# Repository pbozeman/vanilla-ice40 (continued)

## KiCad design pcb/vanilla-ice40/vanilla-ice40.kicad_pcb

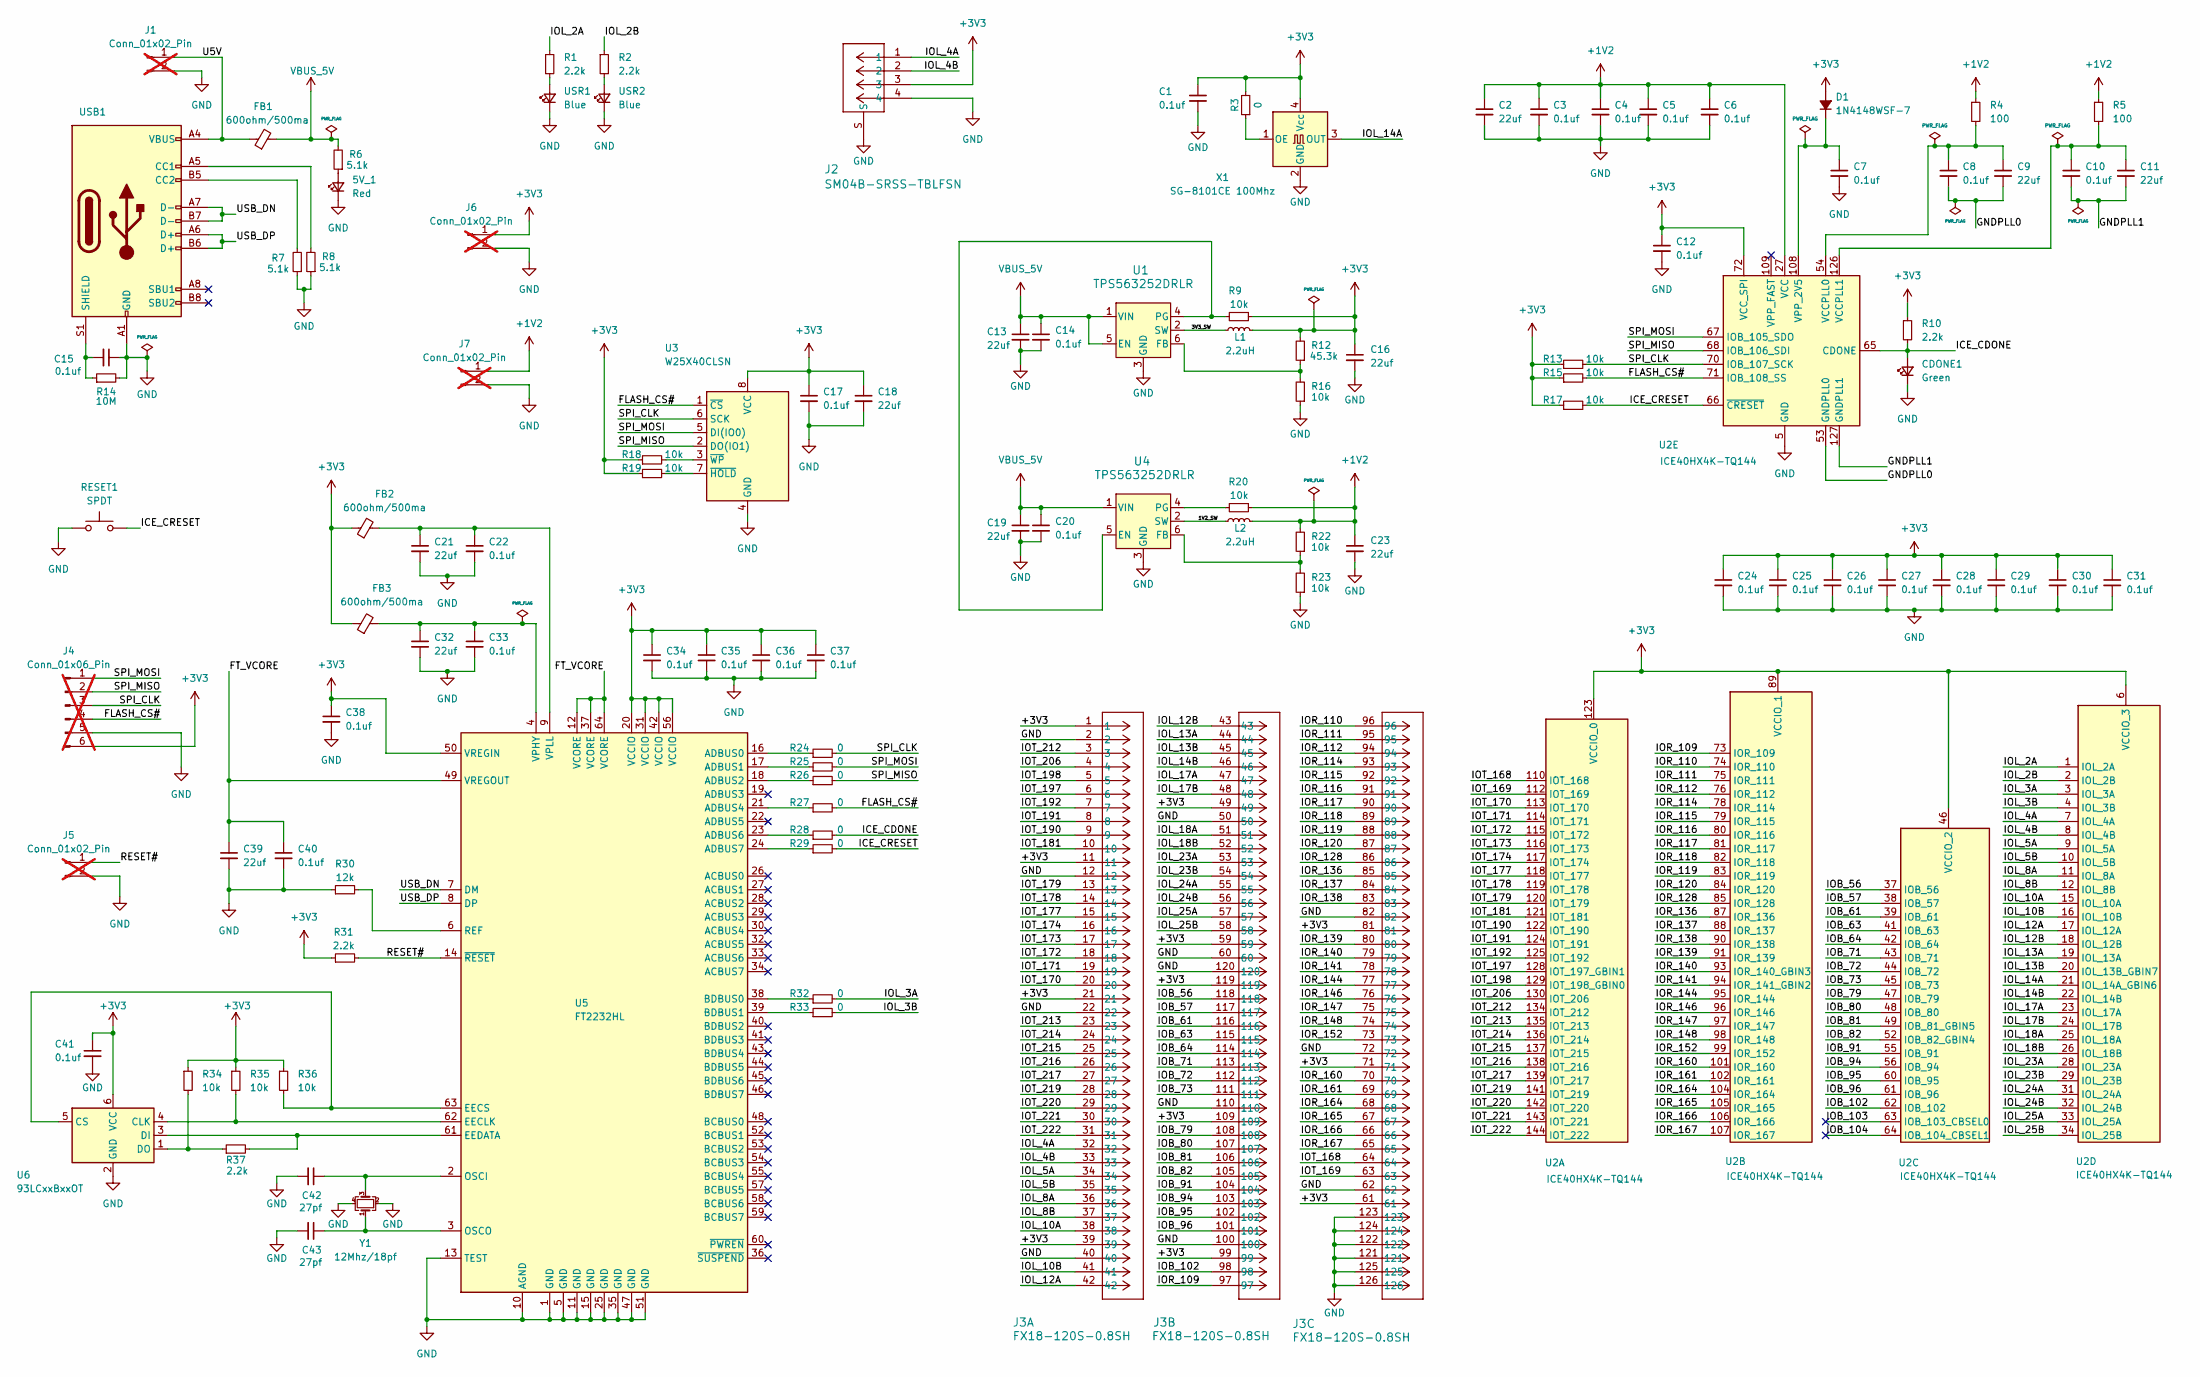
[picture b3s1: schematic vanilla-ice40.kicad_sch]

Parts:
5V_1: Red; D_0603_1608Metric; LCSC Part # C2286
C1, C3, C4, C5, C6, C7, C8, C10, C12, C14, C15, C17, C20, C22, C24, C25, C26, C27, C28, C29, C30, C31, C33, C34, C35, C36, C37, C38, C40, C41: 0.1uf; C_0402_1005Metric; LCSC Part # C1525
C2, C9, C11, C13, C16, C18, C19, C21, C23, C32, C39: 22uf; C_0603_1608Metric; LCSC Part # C59461
C42, C43: 27pf; C_0402_1005Metric; LCSC Part # C1555
CDONE1: Green; D_0603_1608Metric; LCSC Part # C434423
D1: 1N4148WSF-7; D_SOD-323F; LCSC Part # C119617
FB1, FB2, FB3: 600ohm/500ma; L_0603_1608Metric; LCSC Part # C1002
J1, J5, J6, J7: Conn_01x02_Pin; PinHeader_1x02_P2.54mm_Vertical; not fitted
J2: SM04B-SRSS-TBLFSN; CONN_SM04B_JST; LCSC Part # C160404
J3: FX18-120S-0.8SH; CUSTOM_FX_120S-0.8SH20; LCSC Part # C598059
J4: Conn_01x06_Pin; PinHeader_1x06_P2.54mm_Vertical; not fitted
L1, L2: 2.2uH; L_1008_2520Metric; LCSC Part # C391305
R1, R2, R10, R31, R37: 2.2k; R_0603_1608Metric; LCSC Part # C4190
R3, R24, R25, R26, R27, R28, R29, R32, R33: 0; R_0603_1608Metric; LCSC Part # C21189
R4, R5: 100; R_0603_1608Metric; LCSC Part # C22775
R6, R7, R8: 5.1k; R_0603_1608Metric; LCSC Part # C23186
R9, R13, R15, R16, R17, R18, R19, R20, R22, R23, R34, R35, R36: 10k; R_0603_1608Metric; LCSC Part # C25804
R12: 45.3k; R_0603_1608Metric; LCSC Part # C23058
R14: 10M; R_0603_1608Metric; LCSC Part # C7250
R30: 12k; R_0603_1608Metric; LCSC Part # C22790
RESET1: SPDT; SW_SPST_PTS810; LCSC Part # C221897
U1, U4: TPS563252DRLR; SOT6_DRL_TEX; LCSC Part # C19188399
U2: ICE40HX4K-TQ144; TQFP-144_20x20mm_P0.5mm; LCSC Part # C1521989
U3: W25X40CLSN; SOIC-8_3.9x4.9mm_P1.27mm; LCSC Part # C19617
U5: FT2232HL; LQFP-64_10x10mm_P0.5mm; LCSC Part # C27882
U6: 93LCxxBxxOT; SOT-23-6; LCSC Part # C190271
USB1: USB_C_Receptacle_USB2.0_16P; USB_C_Receptacle_GCT_USB4105-xx-A_16P_TopMnt_Horizontal; LCSC Part # C2686968
USR1, USR2: Blue; D_0603_1608Metric; LCSC Part # C965807
X1: SG-8101CE 100Mhz; Oscillator_SMD_SeikoEpson_SG8002CE-4Pin_3.2x2.5mm; LCSC Part # C390559
Y1: 12Mhz/18pf; Crystal_SMD_3225-4Pin_3.2x2.5mm; LCSC Part # C390764

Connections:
+1V2: C2.1, C3.1, C4.1, C5.1, C6.1, C23.1, J7.1, L2.2, R4.1, R5.1, R20.1, R22.2, U2.27 (VCC), U2.40 (VCC), U2.92 (VCC), U2.111 (VCC)
+3V3: C1.1, C12.1, C16.1, C17.1, C18.1, C24.1, C25.1, C26.1, C27.1, C28.1, C29.1, C30.1, C31.1, C34.1, C35.1, C36.1, C37.1, C38.1, C41.1, D1.2 (A), FB2.1, FB3.1, J2.3, J3.1, J3.11, J3.21, J3.39, J3.49, J3.59, J3.61, J3.71, J3.81, J3.99, J3.109, J3.119, J4.6, J6.1, L1.2, R3.2, R9.1, R10.1, R12.2, R13.1, R15.1, R17.1, R18.1, R19.1, R31.1, R34.1, R35.1, R36.1, U2.6 (VCCIO_3), U2.30 (VCCIO_3), U2.46 (VCCIO_2), U2.57 (VCCIO_2), U2.72 (VCC_SPI), U2.89 (VCCIO_1), U2.100 (VCCIO_1), U2.123 (VCCIO_0), U2.131 (VCCIO_0), U3.8 (VCC), U5.20 (VCCIO), U5.31 (VCCIO), U5.42 (VCCIO), U5.50 (VREGIN), U5.56 (VCCIO), U6.6 (VCC), X1.4 (Vcc)
/1V2_SW: L2.1, U4.2 (SW)
/3V3_SW: L1.1, U1.2 (SW)
/FLASH_CS#: J4.4, R15.2, R27.2, U2.71 (IOB_108_SS), U3.1 (~CS)
/FT_VCORE: C39.1, C40.1, U5.12 (VCORE), U5.37 (VCORE), U5.49 (VREGOUT), U5.64 (VCORE)
/GNDPLL0: C8.2, C9.2, U2.53 (GNDPLL0)
/GNDPLL1: C10.2, C11.2, U2.127 (GNDPLL1)
/ICE_CDONE: CDONE1.2 (A), R10.2, R28.2, U2.65 (CDONE)
/ICE_CRESET: R17.2, R29.2, RESET1.2, U2.66 (~CRESET)
/IOB_56: J3.118, U2.37 (IOB_56)
/IOB_57: J3.117, U2.38 (IOB_57)
/IOB_61: J3.116, U2.39 (IOB_61)
/IOB_63: J3.115, U2.41 (IOB_63)
/IOB_64: J3.114, U2.42 (IOB_64)
/IOB_71: J3.113, U2.43 (IOB_71)
/IOB_72: J3.112, U2.44 (IOB_72)
/IOB_73: J3.111, U2.45 (IOB_73)
/IOB_79: J3.108, U2.47 (IOB_79)
/IOB_80: J3.107, U2.48 (IOB_80)
/IOB_81: J3.106, U2.49 (IOB_81_GBIN5)
/IOB_82: J3.105, U2.52 (IOB_82_GBIN4)
/IOB_91: J3.104, U2.55 (IOB_91)
/IOB_94: J3.103, U2.56 (IOB_94)
/IOB_95: J3.102, U2.60 (IOB_95)
/IOB_96: J3.101, U2.61 (IOB_96)
/IOB_102: J3.98, U2.62 (IOB_102)
/IOB_103: U2.63 (IOB_103_CBSEL0)
/IOB_104: U2.64 (IOB_104_CBSEL1)
/IOL_2A: R1.1, U2.1 (IOL_2A)
/IOL_2B: R2.1, U2.2 (IOL_2B)
/IOL_3A: R32.2, U2.3 (IOL_3A)
/IOL_3B: R33.2, U2.4 (IOL_3B)
/IOL_4A: J2.1, J3.32, U2.7 (IOL_4A)
/IOL_4B: J2.2, J3.33, U2.8 (IOL_4B)
/IOL_5A: J3.34, U2.9 (IOL_5A)
/IOL_5B: J3.35, U2.10 (IOL_5B)
/IOL_8A: J3.36, U2.11 (IOL_8A)
/IOL_8B: J3.37, U2.12 (IOL_8B)
/IOL_10A: J3.38, U2.15 (IOL_10A)
/IOL_10B: J3.41, U2.16 (IOL_10B)
/IOL_12A: J3.42, U2.17 (IOL_12A)
/IOL_12B: J3.43, U2.18 (IOL_12B)
/IOL_13A: J3.44, U2.19 (IOL_13A)
/IOL_13B: J3.45, U2.20 (IOL_13B_GBIN7)
/IOL_14A: U2.21 (IOL_14A_GBIN6), X1.3 (OUT)
/IOL_14B: J3.46, U2.22 (IOL_14B)
/IOL_17A: J3.47, U2.23 (IOL_17A)
/IOL_17B: J3.48, U2.24 (IOL_17B)
/IOL_18A: J3.51, U2.25 (IOL_18A)
/IOL_18B: J3.52, U2.26 (IOL_18B)
/IOL_23A: J3.53, U2.28 (IOL_23A)
/IOL_23B: J3.54, U2.29 (IOL_23B)
/IOL_24A: J3.55, U2.31 (IOL_24A)
/IOL_24B: J3.56, U2.32 (IOL_24B)
/IOL_25A: J3.57, U2.33 (IOL_25A)
/IOL_25B: J3.58, U2.34 (IOL_25B)
/IOR_109: J3.97, U2.73 (IOR_109)
/IOR_110: J3.96, U2.74 (IOR_110)
/IOR_111: J3.95, U2.75 (IOR_111)
/IOR_112: J3.94, U2.76 (IOR_112)
/IOR_114: J3.93, U2.78 (IOR_114)
/IOR_115: J3.92, U2.79 (IOR_115)
/IOR_116: J3.91, U2.80 (IOR_116)
/IOR_117: J3.90, U2.81 (IOR_117)
/IOR_118: J3.89, U2.82 (IOR_118)
/IOR_119: J3.88, U2.83 (IOR_119)
/IOR_120: J3.87, U2.84 (IOR_120)
/IOR_128: J3.86, U2.85 (IOR_128)
/IOR_136: J3.85, U2.87 (IOR_136)
/IOR_137: J3.84, U2.88 (IOR_137)
/IOR_138: J3.83, U2.90 (IOR_138)
/IOR_139: J3.80, U2.91 (IOR_139)
/IOR_140: J3.79, U2.93 (IOR_140_GBIN3)
/IOR_141: J3.78, U2.94 (IOR_141_GBIN2)
/IOR_144: J3.77, U2.95 (IOR_144)
/IOR_146: J3.76, U2.96 (IOR_146)
/IOR_147: J3.75, U2.97 (IOR_147)
/IOR_148: J3.74, U2.98 (IOR_148)
/IOR_152: J3.73, U2.99 (IOR_152)
/IOR_160: J3.70, U2.101 (IOR_160)
/IOR_161: J3.69, U2.102 (IOR_161)
/IOR_164: J3.68, U2.104 (IOR_164)
/IOR_165: J3.67, U2.105 (IOR_165)
/IOR_166: J3.66, U2.106 (IOR_166)
/IOR_167: J3.65, U2.107 (IOR_167)
/IOT_168: J3.64, U2.110 (IOT_168)
/IOT_169: J3.63, U2.112 (IOT_169)
/IOT_170: J3.20, U2.113 (IOT_170)
/IOT_171: J3.19, U2.114 (IOT_171)
/IOT_172: J3.18, U2.115 (IOT_172)
/IOT_173: J3.17, U2.116 (IOT_173)
/IOT_174: J3.16, U2.117 (IOT_174)
/IOT_177: J3.15, U2.118 (IOT_177)
/IOT_178: J3.14, U2.119 (IOT_178)
/IOT_179: J3.13, U2.120 (IOT_179)
/IOT_181: J3.10, U2.121 (IOT_181)
/IOT_190: J3.9, U2.122 (IOT_190)
/IOT_191: J3.8, U2.124 (IOT_191)
/IOT_192: J3.7, U2.125 (IOT_192)
/IOT_197: J3.6, U2.128 (IOT_197_GBIN1)
/IOT_198: J3.5, U2.129 (IOT_198_GBIN0)
/IOT_206: J3.4, U2.130 (IOT_206)
/IOT_212: J3.3, U2.134 (IOT_212)
/IOT_213: J3.23, U2.135 (IOT_213)
/IOT_214: J3.24, U2.136 (IOT_214)
/IOT_215: J3.25, U2.137 (IOT_215)
/IOT_216: J3.26, U2.138 (IOT_216)
/IOT_217: J3.27, U2.139 (IOT_217)
/IOT_219: J3.28, U2.141 (IOT_219)
/IOT_220: J3.29, U2.142 (IOT_220)
/IOT_221: J3.30, U2.143 (IOT_221)
/IOT_222: J3.31, U2.144 (IOT_222)
/RESET#: J5.1, R31.2, U5.14 (~RESET)
/SPI_CLK: J4.3, R13.2, R24.2, U2.70 (IOB_107_SCK), U3.6 (SCK)
/SPI_MISO: J4.2, R26.2, U2.68 (IOB_106_SDI), U3.2 (DO(IO1))
/SPI_MOSI: J4.1, R25.2, U2.67 (IOB_105_SDO), U3.5 (DI(IO0))
/U5V: FB1.1, J1.1, USB1.A4 (VBUS), USB1.A9 (VBUS), USB1.B4 (VBUS), USB1.B9 (VBUS)
/USB_DN: U5.7 (DM), USB1.A7 (D-), USB1.B7 (D-)
/USB_DP: U5.8 (DP), USB1.A6 (D+), USB1.B6 (D+)
GND: 5V_1.1 (K), C1.2, C2.2, C3.2, C4.2, C5.2, C6.2, C7.2, C12.2, C13.2, C14.2, C15.1, C16.2, C17.2, C18.2, C19.2, C20.2, C21.2, C22.2, C23.2, C24.2, C25.2, C26.2, C27.2, C28.2, C29.2, C30.2, C31.2, C32.2, C33.2, C34.2, C35.2, C36.2, C37.2, C38.2, C39.2, C40.2, C41.2, C42.2, C43.2, CDONE1.1 (K), J1.2, J2.4, J2.S, J3.2, J3.12, J3.22, J3.40, J3.50, J3.60, J3.62, J3.72, J3.82, J3.100, J3.110, J3.120, J3.121, J3.122, J3.123, J3.124, J3.125, J3.126, J4.5, J5.2, J6.2, J7.2, R7.1, R8.1, R14.2, R16.1, R23.1, R30.1, RESET1.1, U1.3 (GND), U2.5 (GND), U2.13 (GND), U2.14 (GND), U2.59 (GND), U2.69 (GND), U2.86 (GND), U2.103 (GND), U2.132 (GND), U2.140 (GND), U3.4 (GND), U4.3 (GND), U5.1 (GND), U5.5 (GND), U5.10 (AGND), U5.11 (GND), U5.13 (TEST), U5.15 (GND), U5.25 (GND), U5.35 (GND), U5.47 (GND), U5.51 (GND), U6.2 (GND), USB1.A1 (GND), USB1.A12 (GND), USB1.B1 (GND), USB1.B12 (GND), USR1.1 (K), USR2.1 (K), X1.2 (GND), Y1.2, Y1.4
unnamed: 5V_1.2 (A), R6.1
unnamed: C7.1, D1.1 (K), U2.108 (VPP_2V5)
unnamed: R12.1, R16.2, U1.6 (FB)
unnamed: R9.2, U1.4 (PG), U4.5 (EN)
unnamed: C8.1, C9.1, R4.2, U2.54 (VCCPLL0)
unnamed: C10.1, C11.1, R5.2, U2.126 (VCCPLL1)
unnamed: R19.2, U3.7 (~HOLD)
unnamed: R18.2, U3.3 (~WP)
unnamed: R22.1, R23.2, U4.6 (FB)
unnamed: R20.2, U4.4 (PG)
unnamed: R24.1, U5.16 (ADBUS0)
unnamed: R25.1, U5.17 (ADBUS1)
unnamed: R26.1, U5.18 (ADBUS2)
unnamed: R27.1, U5.21 (ADBUS4)
unnamed: R28.1, U5.23 (ADBUS6)
unnamed: R29.1, U5.24 (ADBUS7)
unnamed: R32.1, U5.38 (BDBUS0)
unnamed: R33.1, U5.39 (BDBUS1)
unnamed: R35.2, U5.62 (EECLK), U6.4 (CLK)
unnamed: R36.2, U5.63 (EECS), U6.5 (CS)
unnamed: R37.2, U5.61 (EEDATA), U6.3 (DI)
unnamed: C42.1, U5.2 (OSCI), Y1.3
unnamed: C43.1, U5.3 (OSCO), Y1.1
unnamed: R30.2, U5.6 (REF)
unnamed: C32.1, C33.1, FB3.2, U5.4 (VPHY)
unnamed: C21.1, C22.1, FB2.2, U5.9 (VPLL)
unnamed: R34.2, R37.1, U6.1 (DO)
unnamed: R8.2, USB1.A5 (CC1)
unnamed: R7.2, USB1.B5 (CC2)
unnamed: C15.2, R14.1, USB1.S1 (SHIELD)
unnamed: R1.2, USR1.2 (A)
unnamed: R2.2, USR2.2 (A)
unnamed: R3.1, X1.1 (OE)
VBUS_5V: C13.1, C14.1, C19.1, C20.1, FB1.2, R6.2, U1.1 (VIN), U1.5 (EN), U4.1 (VIN)

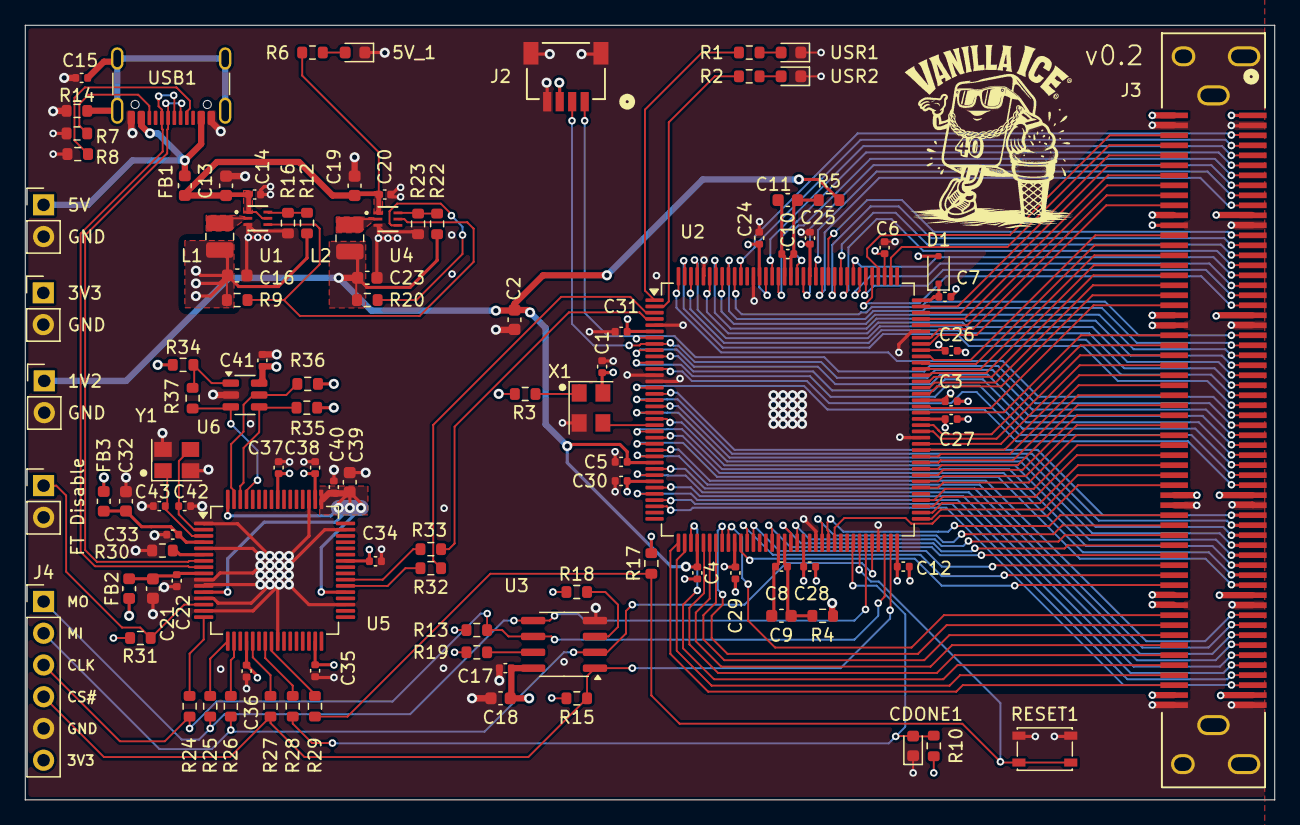
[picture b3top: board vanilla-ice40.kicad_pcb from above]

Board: 4 copper layers, 100.0 x 62.0 mm, 105 parts (0 on the bottom side), 153 nets.
